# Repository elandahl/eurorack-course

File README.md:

# eurorack-course
Analog Electronics course featuring Eurorack modular synth project

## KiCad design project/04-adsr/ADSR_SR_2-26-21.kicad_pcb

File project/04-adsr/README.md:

# 🎚️ ADSR Envelope Generator

**Project 04 – Modular Synthesizer Course**

This Eurorack-compatible module implements an **ADSR (Attack, Decay, Sustain, Release)** envelope generator using a **TLC555 CMOS timer**, op-amps, discrete transistors, and a shaping network of resistors, capacitors, and diodes. When triggered by a gate signal, it produces a control voltage that follows a classic ADSR shape used to control VCAs, filters, or pitch over time in a modular synthesizer.

The design is adapted from [René Schmitz’s "Fastest Envelope in the West"](https://www.schmitzbits.de/adsr.html), simplified for modern components and student assembly.

---

## 🔁 How It Works

The four phases:

- **Attack** – how quickly the voltage rises to its peak when a gate is received  
- **Decay** – how quickly it falls to the sustain level after the attack  
- **Sustain** – the level held while the gate is high  
- **Release** – how quickly the envelope falls to zero after the gate ends  

A CMOS 555 timer (TLC555) generates a fixed-duration logic pulse that controls a capacitor (C3) charged and discharged through different RC paths. Diodes steer current direction for each phase, and an op-amp buffers the output.

---

## 🧰 Schematic Overview

Below is the schematic for the ADSR Envelope Generator (`ADSR_SR_2-26-21`):

---

## 📁 Circuit and Design Files

This folder includes the full set of KiCad source files:

- `ADSR_SR_2-26-21.sch` – Schematic (KiCad)
- `ADSR_SR_2-26-21.kicad_pcb` – PCB layout (KiCad)
- `ADSR_SR_2-26-21.csv` – Bill of Materials (BOM)
- `ADSR_SR_2-26-21-backups/` – Backup and autosave files
- `.lib`, `.dcm`, `.pro`, `.net`, `.xml` – Supporting KiCad project data

---

## 🧾 Bill of Materials (BOM)

| Qty | Component            | Value        | Notes                          |
|-----|----------------------|--------------|---------------------------------|
| 1   | Timer IC             | TLC555       | CMOS version (not NE555)        |
| 1   | Op-Amp               | TL072        | Dual op-amp, buffer and divider |
| 3   | NPN Transistor       | 2N3904       | Gate pulse shaping              |
| 3   | Potentiometer        | 1 MΩ Linear  | Attack, Decay, Release          |
| 1   | Potentiometer        | 10k Linear   | Sustain   
| 1   | Capacitor (polarized)| 10 µF        | TLC555 timing cap               |
| 1   | Capacitor (bipolar)  | 2.2 µF       | Envelope integrator             |
| 7   | Capacitor (ceramic)  | 10 nF        | Supply and signal decoupling         |
| 3   | Resistor             | 220 Ω        | Series with A/D/R pots          |
| 2   | Resistor             | 10 kΩ        | Input and transistor base         |
| 4   | Resistors            | 4.7 kΩ       | Transistor bias, 555 pull-up    |
| 1   | Resistor             | 22 kΩ        | Transistor base drive          
| 1   | Resistor             | 1 MΩ         | 555 reset                      
| 1   | Resistor             | 2.2 kΩ       | LED current limit                      
| 5   | Diodes               | 1N4148       | Signal steering (A/D/R + reset) |
| 1   | Red LED              | Oval         | Output indicator               
| 1   | Pushbutton Switch    | N.O.         | Manual trigger                 
| 1   | IDC Header           | 10-pin (ML10)| Eurorack power                  |

---

## 🛠️ Assembly Guide (with Photos)

Step-by-step build documentation is available here:

📷 [Google Drive – ADSR Assembly Photos](https://drive.google.com/drive/folders/1wlfnccw4EV9Ylf7Mrc6TivC7RlBOovWM?usp=sharing)

This includes high-res annotated photos, component placement, and tips for first-time solderers.

---

## 📊 Analysis & Simulation

An in-depth analysis of the ADSR envelope shaping and RC time constants is provided here:

🔍 [ADSR Technical Analysis](./analysis.md)

Simulation tools using [LushProjects](https://lushprojects.org/circuitjs/) can help visualize:

- [Gate trigger + transistor shaper](https://tinyurl.com/y66v7bsb)  
- [Full ADSR timing circuit](https://tinyurl.com/y358uu4k)

---

## 🕰️ Legacy Files

The folder includes earlier schematic files and alternate circuit variants:

- `ADSR.sch`, `ADSR.pro`, etc. — original Eagle-imported designs
- `sequencer.*` files — not used in this project
- `.bak`, `.xml`, `.net` — backup and compiler artifacts

These are included for historical completeness and archival.

---

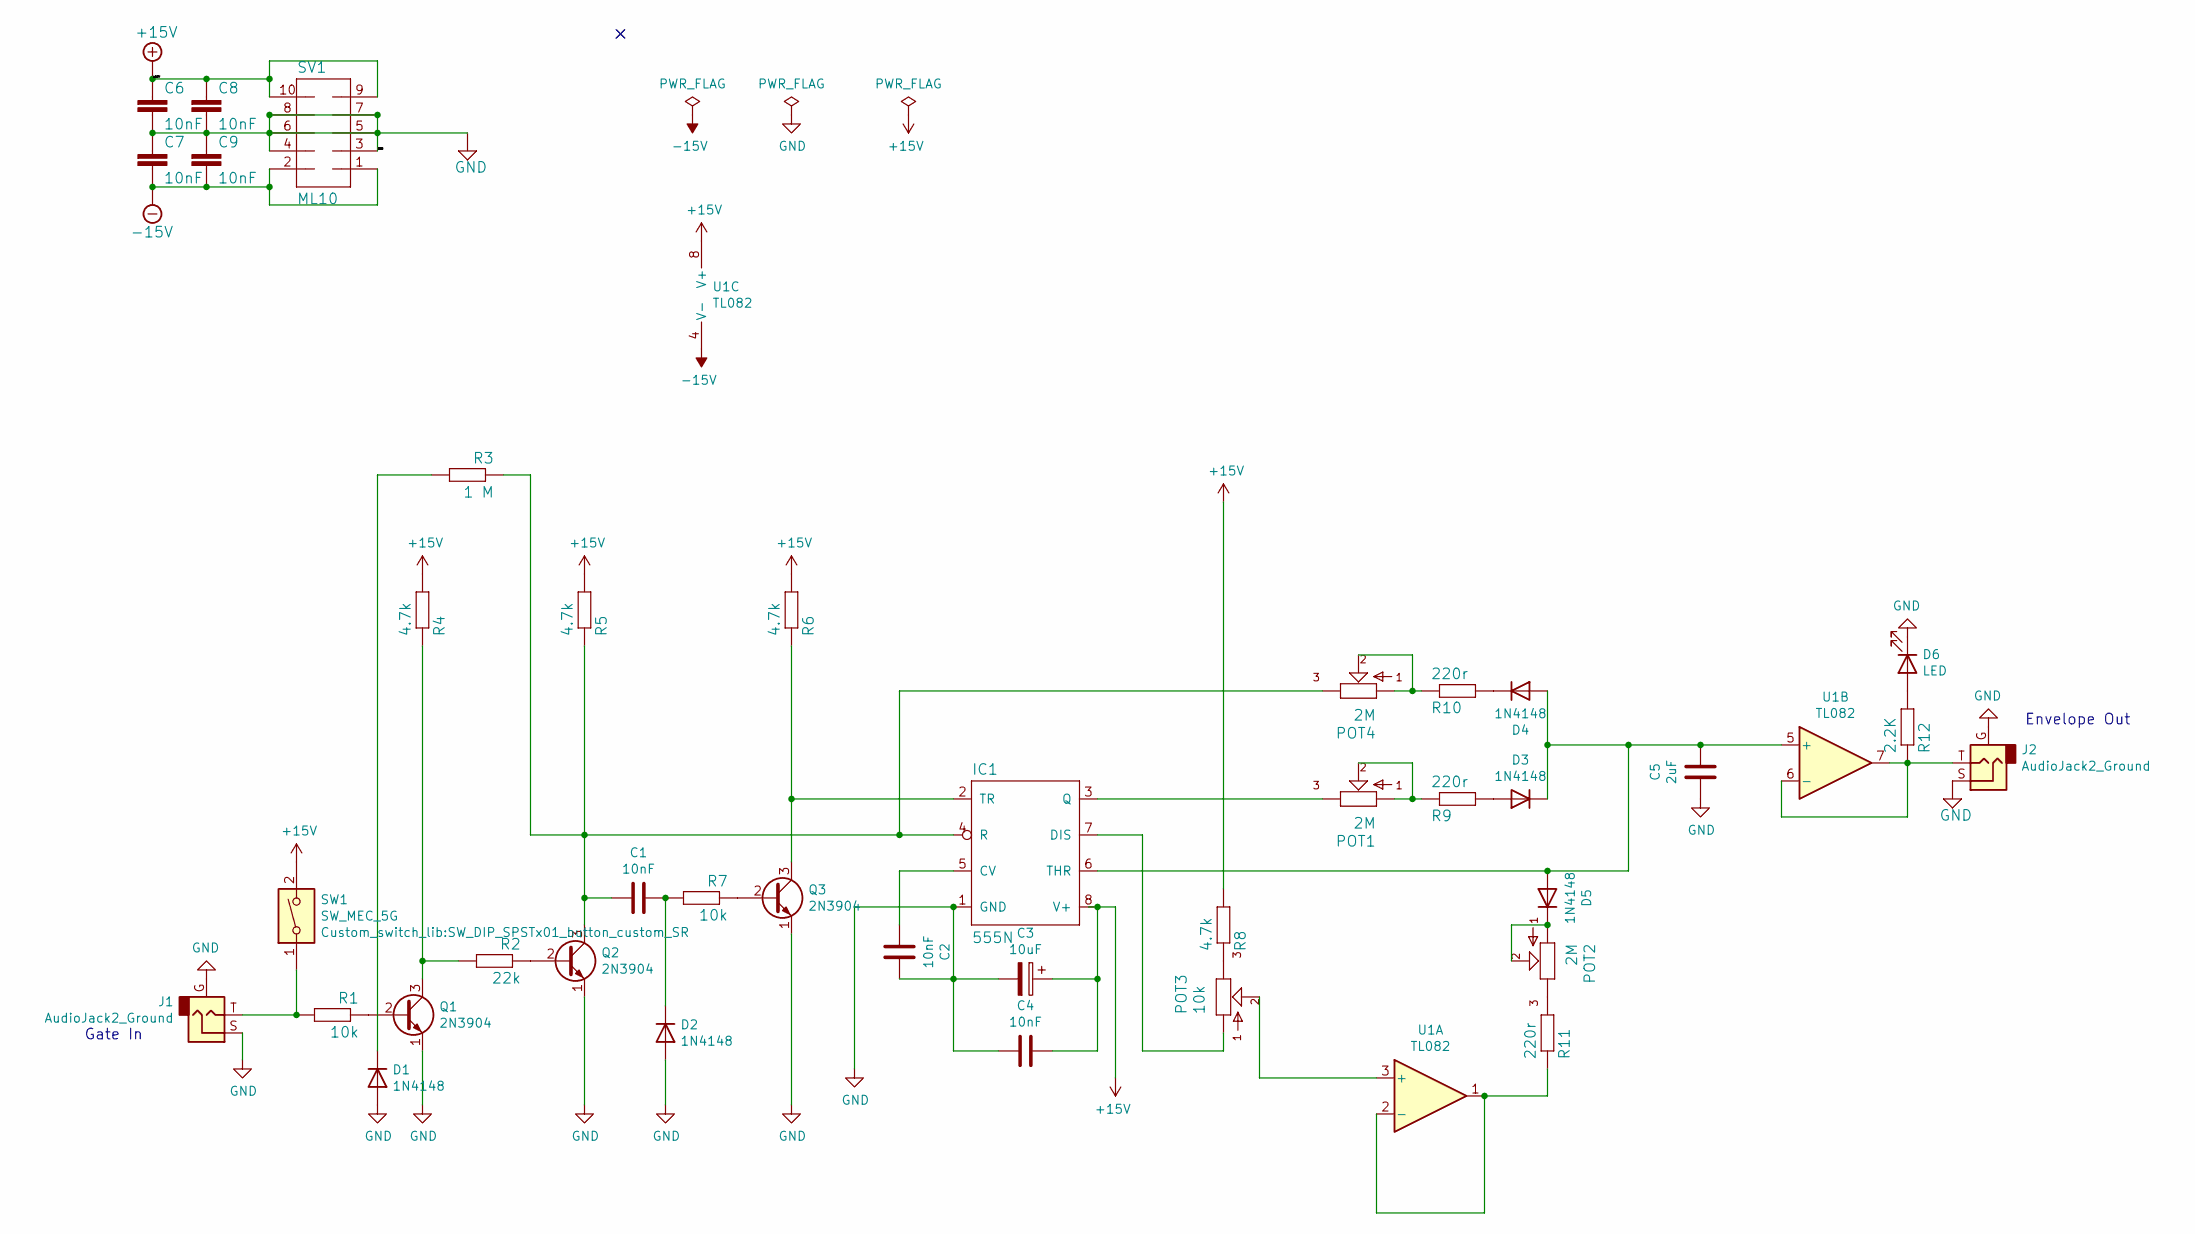
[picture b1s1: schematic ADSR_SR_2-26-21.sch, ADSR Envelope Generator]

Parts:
C1, C2, C4, C6, C7, C8, C9: 10nF; C_Rect_L7.0mm_W2.0mm_P5.00mm
C3: 10uF; CP_Radial_D5.0mm_P2.00mm
C5: 2uF; C_Rect_L7.0mm_W2.0mm_P5.00mm
D1, D2, D3, D4, D5: 1N4148; D_DO-35_SOD27_P7.62mm_Horizontal
D6: LED; LED_D3.0mm
IC1: 555N; DIP-8_W7.62mm
J1, J2: AudioJack2_Ground; Jack_3.5mm_QingPu_WQP-PJ398SM_Vertical_CircularHoles
POT1, POT2, POT4: 2M; Potentiometer_Alpha_RD901F-40-00D_Single_Vertical
POT3: 10k; Potentiometer_Alpha_RD901F-40-00D_Single_Vertical
Q1, Q2, Q3: 2N3904; TO-92L_Inline_Wide
R1, R7: 10k; R_Axial_DIN0207_L6.3mm_D2.5mm_P10.16mm_Horizontal
R2: 22k; R_Axial_DIN0207_L6.3mm_D2.5mm_P10.16mm_Horizontal
R3: 1 M; R_Axial_DIN0207_L6.3mm_D2.5mm_P10.16mm_Horizontal
R4, R5, R6, R8: 4.7k; R_Axial_DIN0207_L6.3mm_D2.5mm_P10.16mm_Horizontal
R9, R10, R11: 220r; R_Axial_DIN0207_L6.3mm_D2.5mm_P10.16mm_Horizontal
R12: 2.2K; R_Axial_DIN0207_L6.3mm_D2.5mm_P10.16mm_Horizontal
SV1: ML10; IDC-Header_2x05_P2.54mm_Latch_Vertical
SW1: SW_MEC_5G; SW_DIP_SPSTx01_button_custom_SR
U1: TL082; DIP-8_W7.62mm

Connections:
+15V: C3.1, C4.1, C6.1, C8.1, IC1.8 (V+), R4.2, R5.2, R6.2, R8.2, SV1.9, SV1.10, SW1.2, U1.8 (V+)
-15V: C7.2, C9.2, SV1.1, SV1.2, U1.4 (V-)
GND: C2.1, C3.2, C4.2, C5.2, C6.2, C7.1, C8.2, C9.1, D1.2 (A), D2.2 (A), D6.1 (K), IC1.1 (GND), J1.G, J1.S, J2.G, J2.S, Q1.1 (E), Q2.1 (E), Q3.1 (E), SV1.3, SV1.4, SV1.5, SV1.6, SV1.7, SV1.8
unnamed: C1.1, D2.1 (K), R7.2
unnamed: C1.2, IC1.4 (R), POT4.3, Q2.3 (C), R3.1, R5.1
unnamed: C2.2, IC1.5 (CV)
unnamed: C5.1, D3.1 (K), D4.2 (A), D5.2 (A), IC1.6 (THR), U1.5 (+)
unnamed: D1.1 (K), R3.2
unnamed: D3.2 (A), R9.2
unnamed: D4.1 (K), R10.2
unnamed: D5.1 (K), POT2.1, POT2.2
unnamed: D6.2 (A), R12.2
unnamed: IC1.2 (TR), Q3.3 (C), R6.1
unnamed: IC1.3 (Q), POT1.3
unnamed: IC1.7 (DIS), POT3.1
unnamed: J1.T, R1.2, SW1.1
unnamed: J2.T, R12.1, U1.6 (-), U1.7
unnamed: POT1.1, POT1.2, R9.1
unnamed: POT2.3, R11.2
unnamed: POT3.2, U1.3 (+)
unnamed: POT3.3, R8.1
unnamed: POT4.1, POT4.2, R10.1
unnamed: Q1.2 (B), R1.1
unnamed: Q1.3 (C), R2.2, R4.1
unnamed: Q2.2 (B), R2.1
unnamed: Q3.2 (B), R7.1
unnamed: R11.1, U1.1, U1.2 (-)

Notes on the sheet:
Gate In
Envelope Out

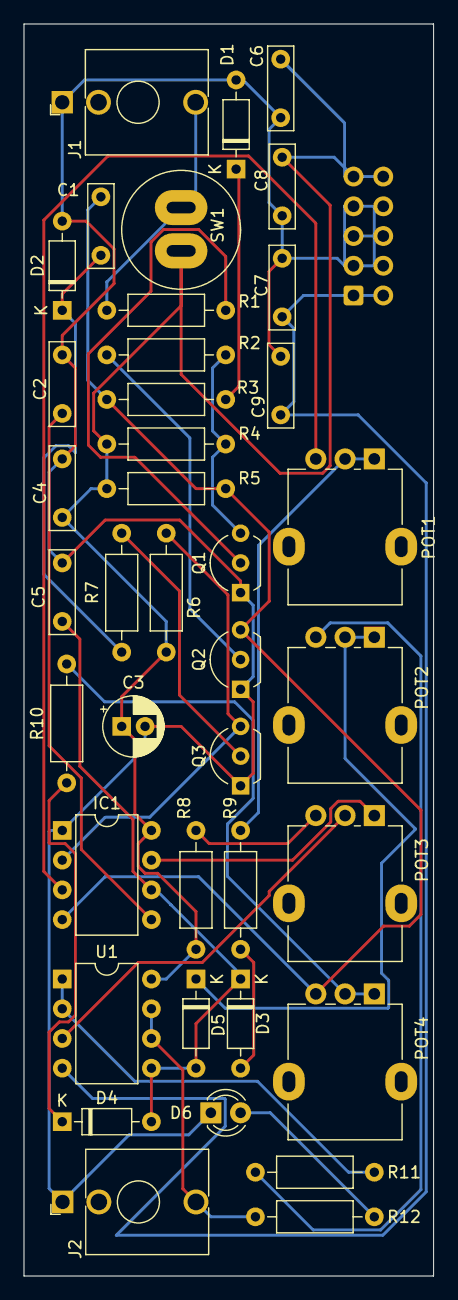
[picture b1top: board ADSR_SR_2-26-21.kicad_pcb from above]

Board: 2 copper layers, 35.0 x 107.0 mm, 40 parts (1 on the bottom side), 27 nets.

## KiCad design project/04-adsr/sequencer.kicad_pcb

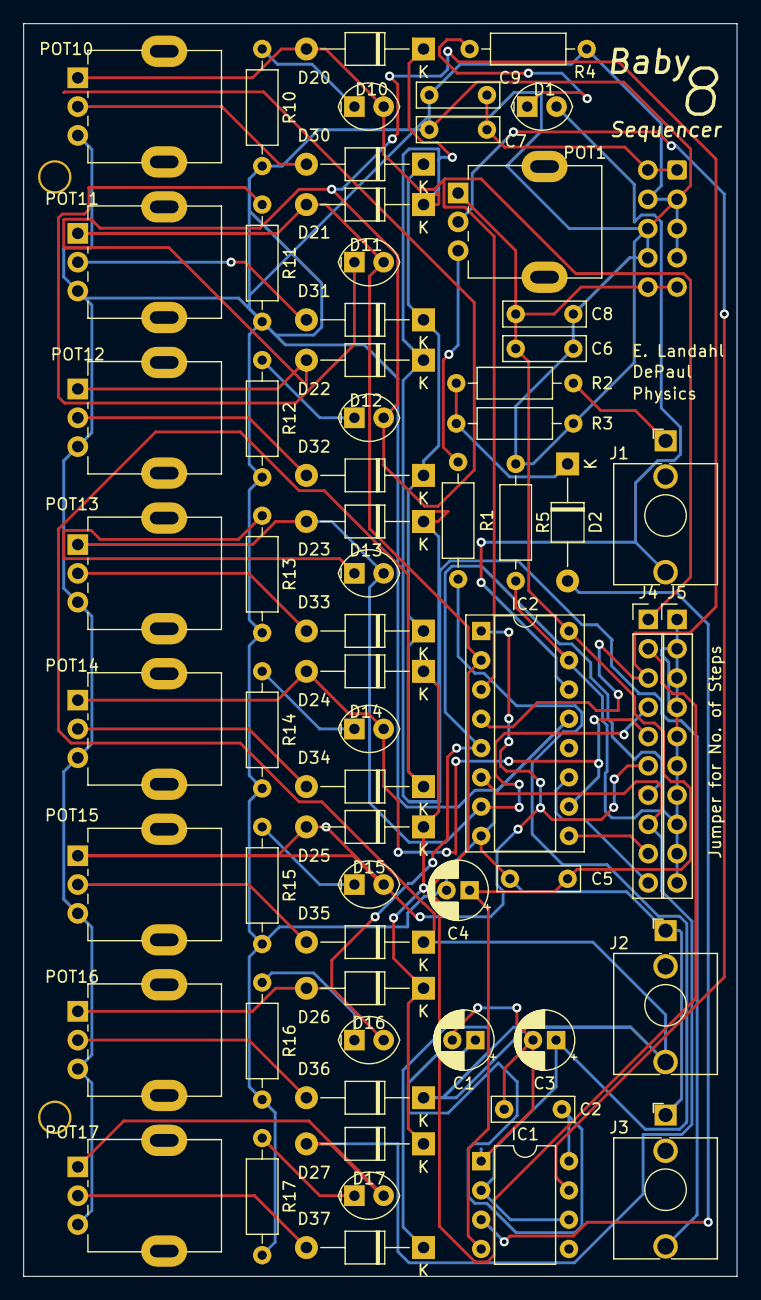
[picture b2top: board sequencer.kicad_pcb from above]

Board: 2 copper layers, 61.9 x 108.7 mm, 65 parts (1 on the bottom side), 42 nets.

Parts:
C1, C4: 10uF; CP_Radial_D5.0mm_P2.00mm
C2, C5, C6, C7, C8, C9: 10nF; C_Rect_L7.0mm_W2.0mm_P5.00mm
C3: 22uF; CP_Radial_D5.0mm_P2.00mm
D1, D10, D11, D12, D13, D14, D15, D16, D17: LED; LED_Oval_W5.2mm_H3.8mm
D2, D20, D21, D22, D23, D24, D25, D26, D27, D30, D31, D32, D33, D34, D35, D36, D37: D; D_T-1_P10.16mm_Horizontal
IC1: 555N; DIP-8_W7.62mm
IC2: 4017; DIP-16_W7.62mm_Socket
J1, J2, J3: AudioJack2_Ground; Jack_3.5mm_QingPu_WQP-PJ398SM_Vertical_CircularHoles
J4, J5: Conn_01x10; PinHeader_1x10_P2.54mm_Vertical
POT1, POT10, POT11, POT12, POT13, POT14, POT15, POT16, POT17: 100k; Potentiometer_Alpha_RD901F-40-00D_Single_Vertical
R1: 1k; R_Axial_DIN0207_L6.3mm_D2.5mm_P10.16mm_Horizontal
R2: 10k; R_Axial_DIN0207_L6.3mm_D2.5mm_P10.16mm_Horizontal
R3: 100k; R_Axial_DIN0207_L6.3mm_D2.5mm_P10.16mm_Horizontal
R4, R10, R11, R12, R13, R14, R15, R16, R17: 2.2k; R_Axial_DIN0207_L6.3mm_D2.5mm_P10.16mm_Horizontal
R5: 51k; R_Axial_DIN0207_L6.3mm_D2.5mm_P10.16mm_Horizontal
SV1: ML10; IDC-Header_2x05_P2.54mm_Latch_Vertical

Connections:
+15V: C4.1, C5.1, C6.1, C8.1, IC1.4, IC2.16, POT1.1, SV1.9, SV1.10
-15V: C7.2, C9.2, SV1.1, SV1.2
GND: C4.2, C5.2, C6.2, C7.1, C8.2, C9.1, IC2.8, IC2.13, J2.S, J3.S, POT10.3, POT11.3, POT12.3, POT13.3, POT14.3, POT15.3, POT16.3, POT17.3, R3.1, R4.2, R5.1, R10.2, R11.2, R12.2, R13.2, R14.2, R15.2, R16.2, R17.2, SV1.3, SV1.4, SV1.5, SV1.6, SV1.7, SV1.8
unnamed: C1.1, C2.1, IC1.8
unnamed: C1.2, C2.2, C3.2, IC1.1
unnamed: C3.1, IC1.2, IC1.6, R1.1
unnamed: D1.1, R4.1
unnamed: D1.2, IC2.14, J1.T
unnamed: D2.1, R2.2, R3.2
unnamed: D2.2, IC1.3
unnamed: D10.1, R10.1
unnamed: D10.2, D20.2, IC2.3, J4.1, POT10.1
unnamed: D11.1, R11.1
unnamed: D11.2, D21.2, IC2.2, J4.2, POT11.1
unnamed: D12.1, R12.1
unnamed: D12.2, D22.2, IC2.4, J4.3, POT12.1
unnamed: D13.1, R13.1
unnamed: D13.2, D23.2, IC2.7, J4.4, POT13.1
unnamed: D14.1, R14.1
unnamed: D14.2, D24.2, IC2.10, J4.5, POT14.1
unnamed: D15.1, R15.1
unnamed: D15.2, D25.2, IC2.1, J4.6, POT15.1
unnamed: D16.1, R16.1
unnamed: D16.2, D26.2, IC2.5, J4.7, POT16.1
unnamed: D17.1, R17.1
unnamed: D17.2, D27.2, IC2.6, J4.8, POT17.1
unnamed: D20.1, D21.1, D22.1, D23.1, D24.1, D25.1, D26.1, D27.1, J3.T
unnamed: D30.1, D31.1, D32.1, D33.1, D34.1, D35.1, D36.1, D37.1, J2.T
unnamed: D30.2, POT10.2
unnamed: D31.2, POT11.2
unnamed: D32.2, POT12.2
unnamed: D33.2, POT13.2
unnamed: D34.2, POT14.2
unnamed: D35.2, POT15.2
unnamed: D36.2, POT16.2
unnamed: D37.2, POT17.2
unnamed: IC1.7, POT1.2
unnamed: IC2.9, J4.9
unnamed: IC2.11, J4.10
unnamed: IC2.15, J5.1, J5.2, J5.3, J5.4, J5.5, J5.6, J5.7, J5.8, J5.9, J5.10, R5.2
unnamed: J1.S, R2.1
unnamed: POT1.3, R1.2

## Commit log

2025-04-06 Initial repo with flowchart and project modules
2025-04-06 Use full GitHub URLs for clickable flowchart links
2025-04-06 Add ADSR, VCA, and VCO modules to flowchart and file structure
2025-04-06 Add full power supply module README with videos and links
2025-04-06 Organized faceplate files into subdirectories
2025-04-06 Updated README for power supply faceplate structure
2025-04-06 Clean up .DS_Store files and update .gitignore
2025-04-06 Add .ai files to .gitignore
2025-04-06 Add rack assembly video links and organize side panel files
2025-04-06 Update course flowchart with concepts, tools, and custom module
2025-04-06 Add directories and README.md files for Custom Module, KiCAD, and Electronics content
2025-04-06 Add Laser Cutting and Faceplate Design tools with flowchart links and dependencies
2025-04-06 Move lecture slides for DC Equivalent Circuits into slides/ subdirectory
2025-04-06 Add cross-links to Op-Amps, ADSR, White Noise Generator from DC Equivalent Circuits
2025-04-08 Update flowchart Laser -> Noise
2025-04-08 Update flowchart Faceplate -> Noise
2025-04-11 Add White Noise Generator Files
2025-04-14 Updated side panel notes
2025-04-14 Updated side panel notes fix
2025-04-14 Add eurorack power cable pinout
2025-04-19 Improve White Noise Generator README with BOM, transistor info, and image references
2025-04-19 Update White Noise Generator README with prerequisites from flowchart
2025-04-19 Add filter analysis subpage with RC variation plot
2025-04-19 Add updated filter analysis with embedded formula images and Octave plot
2025-04-19 Add ADSR module documentation, KiCad source files, BOM, and assembly photo link
2025-04-19 Add ADSR schematic image and fix 2uF capacitor value
2025-04-19 Add ADSR circuit analysis
2025-04-19 Add ADSR video and simulations
2025-04-20 Update README.md with correct ADSR description and BOM
2025-04-23 Update README.md ADSR BOM
2025-04-23 Update README.md ADSR BOM removed extra diodes
2025-04-23 Update README.md ADSR BOM format
2025-04-25 Added 10k pot and 5th diode to BOM on ADSR
2025-04-28 Updated Op-Amps README with links to slides, videos, and future placeholders
2025-05-05 Renamed README.txt to README.md in Op Amps content
2025-05-05 Added Op Amps 2 slides
2025-05-14 TinkerCad directions for faceplates
2025-05-21 Add VCA KiCAD zip file
2025-06-04 Added VCO KiCAD Zip File
